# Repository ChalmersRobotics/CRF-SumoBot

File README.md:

# CRF nano-sumobot incl crf sumo hat

Please find :

- [instructions and workshop intro (v1.2, updated 251105) -here](https://github.com/ChalmersRobotics/CRF-SumoBot/releases/download/v1.2/CRF.miniSumo.kit.2025.workshop.intro.251105b.pdf)

- [3D manufacturing files](https://github.com/ChalmersRobotics/CRF-SumoBot/releases/download/v1.2/Sumobot.v7.3mf)

[complete release package - here!](https://github.com/ChalmersRobotics/CRF-SumoBot/releases)

# Changelog

| Version     | Changes      |
| ------------- | ------------- |
| v1.2          | <ul><li>Add EN_A and EN_B pins for controlling H-Bridge speed</li><li>Move start module placement slightly more towards the edge</li><li>Add header pins for unused ports on the Arduino to allow further extension / mods</li>Add an optional switch to pull-up and bypass start module</ul> |
| v1.1          | <ul><li>Move mounting holes slightly</li><li>Add header pins for start module</li></ul> |
| v1.0          | First draft |

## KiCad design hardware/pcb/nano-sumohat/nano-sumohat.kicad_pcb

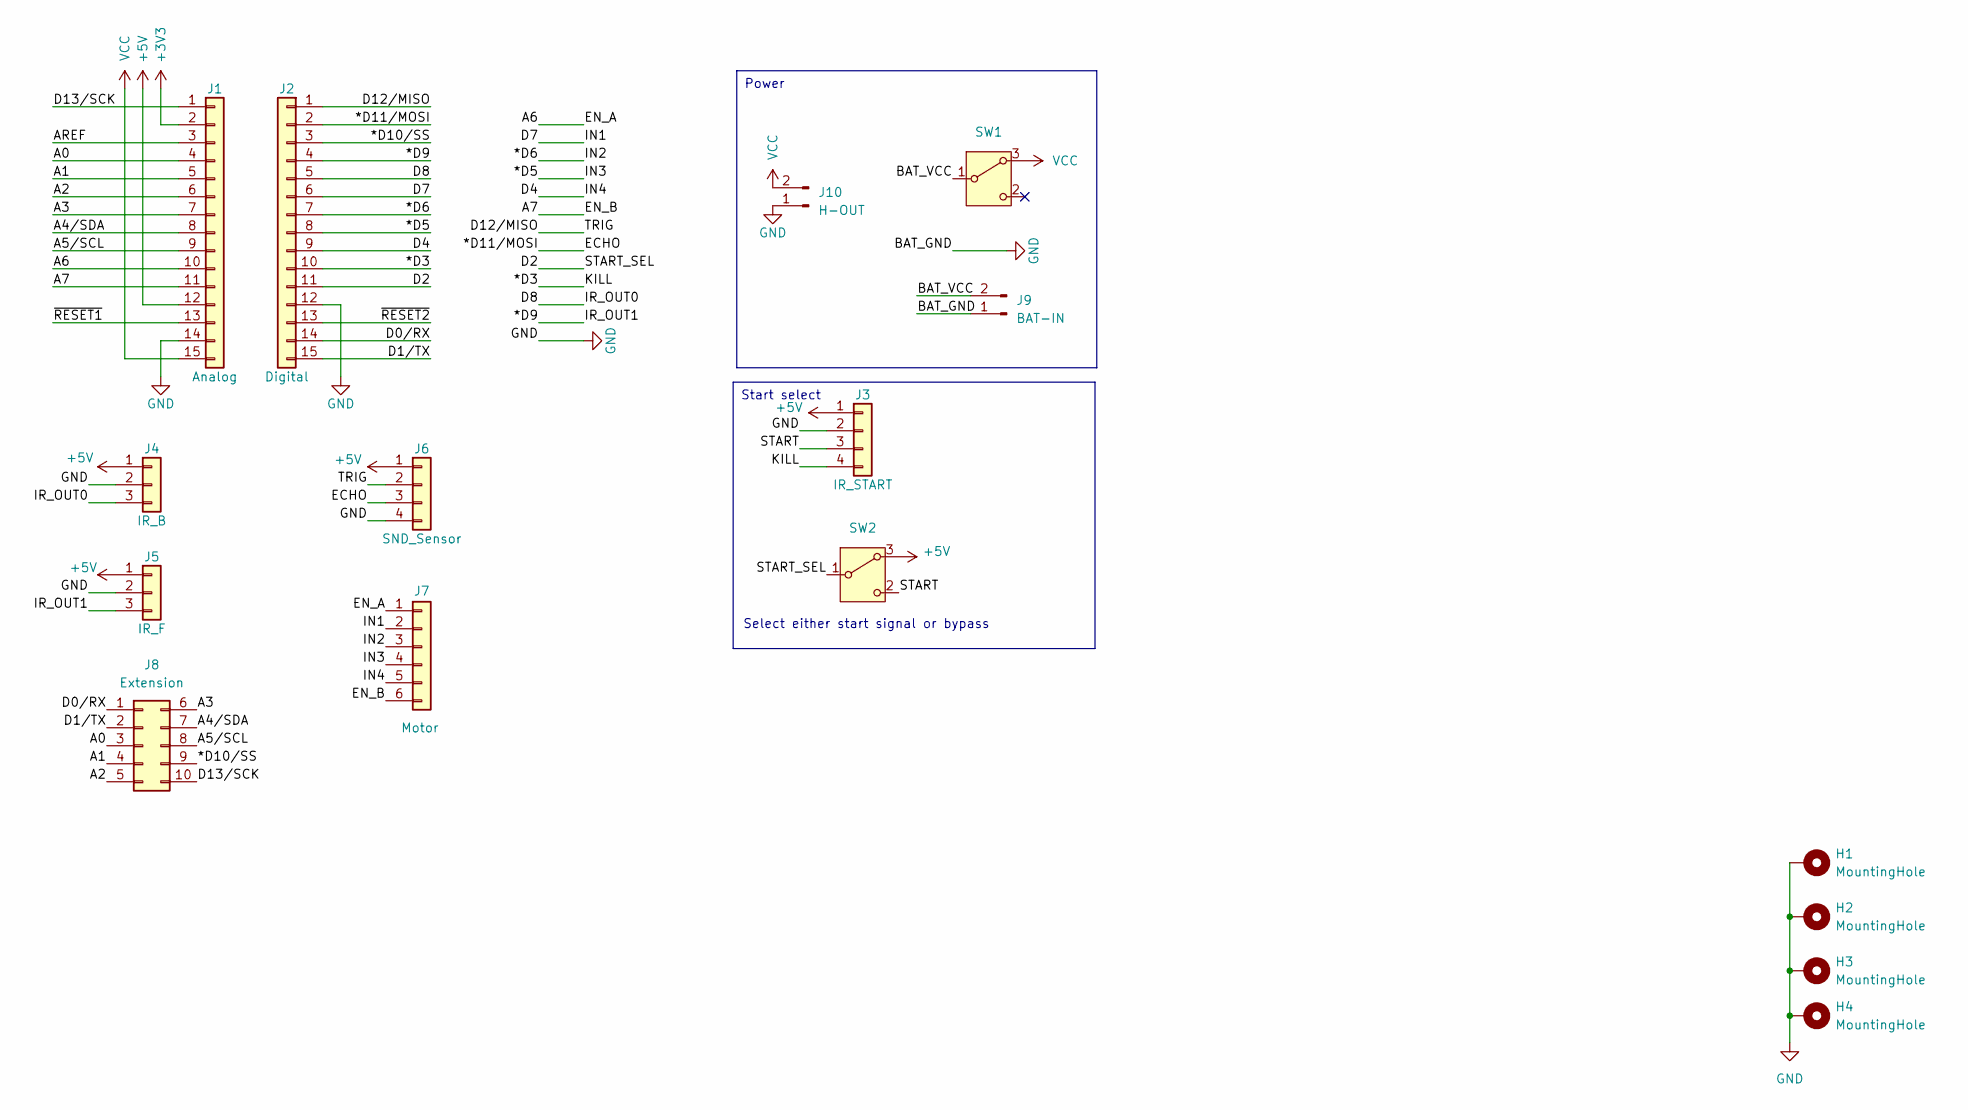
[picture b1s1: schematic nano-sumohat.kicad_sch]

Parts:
H1, H2, H3, H4: MountingHole; MountingHole_2.7mm_M2.5_DIN965_Pad_TopBottom
J1: Analog; PinSocket_1x15_P2.54mm_Vertical
J2: Digital; PinSocket_1x15_P2.54mm_Vertical
J3: IR_START; PinHeader_1x04_P2.54mm_Vertical
J4: IR_B; PinHeader_1x03_P2.54mm_Vertical
J5: IR_F; PinHeader_1x03_P2.54mm_Vertical
J6: SND_Sensor; PinSocket_1x04_P2.54mm_Vertical
J7: Motor; PinHeader_1x06_P2.54mm_Vertical
J8: Extension; PinHeader_2x05_P2.54mm_Vertical
J9: BAT-IN; JST_EH_B2B-EH-A_1x02_P2.50mm_Vertical
J10: H-OUT; JST_EH_B2B-EH-A_1x02_P2.50mm_Vertical
SW1, SW2: SW_Slide-03_Wuerth-WS-SLTV_10x2.5x6.4_P2.54mm

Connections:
+3V3: J1.2
+5V: J1.12, J3.1, J4.1, J5.1, J6.1, SW2.3 (A)
/*D3: J2.10, J3.4
/*D5: J2.8, J7.4
/*D6: J2.7, J7.3
/*D9: J2.4, J5.3
/*D10/SS: J2.3, J8.9
/*D11/MOSI: J2.2, J6.3
/A0: J1.4, J8.3
/A1: J1.5, J8.4
/A2: J1.6, J8.5
/A3: J1.7, J8.6
/A4/SDA: J1.8, J8.7
/A5/SCL: J1.9, J8.8
/A6: J1.10, J7.1
/A7: J1.11, J7.6
/AREF: J1.3
/BAT_VCC: J9.2, SW1.1 (B)
/D0/RX: J2.14, J8.1
/D1/TX: J2.15, J8.2
/D2: J2.11, SW2.1 (B)
/D4: J2.9, J7.5
/D7: J2.6, J7.2
/D8: J2.5, J4.3
/D12/MISO: J2.1, J6.2
/D13/SCK: J1.1, J8.10
/START: J3.3, SW2.2 (C)
/~RESET1: J1.13
/~RESET2: J2.13
GND: H1.1, H2.1, H3.1, H4.1, J1.14, J2.12, J3.2, J4.2, J5.2, J6.4, J9.1, J10.1
VCC: J1.15, J10.2, SW1.3 (A)

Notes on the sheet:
Power
Start select
Select either start signal or bypass

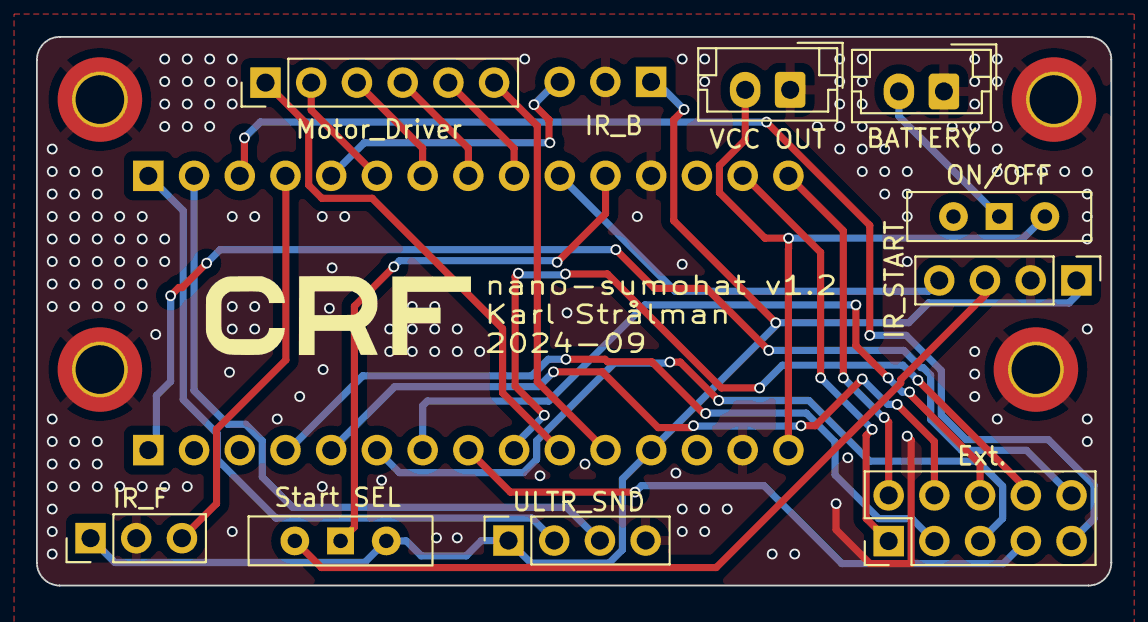
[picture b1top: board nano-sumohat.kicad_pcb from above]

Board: 2 copper layers, 59.7 x 30.5 mm, 16 parts (0 on the bottom side), 27 nets.

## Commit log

2022-11-16 Add sumobot project files
2023-03-18 Add PCB files and restructure repo
    Kicad project files and gerber
2024-03-22 Add gitignore for kicad files
2024-03-22 Add v1.1 for nano sumohat
2024-03-22 Add preview image of sumohat
2024-03-30 Adjust code for nano sumohat 1.1
2024-03-30 Format code
2024-04-02 Refactor code to be somewhat working
2024-04-10 Add comment for when to use old bootloader
2024-04-10 Add guide v2 pdf for sumo build
2024-04-17 Add v2-draft6 build guide
2025-02-01 Remove rendered image of v1.1
2025-02-01 Remove obsolete guide
2025-02-01 Update schematics with more comments
2025-02-01 Remove obsolete readme for schematics
2025-02-01 Add readme with change history
2025-02-05 Bump readme with where to find instructions
2025-02-05 Bump readme with slides
2025-02-05 Replace old 3D files
    Find 3D files in releases
2025-02-05 Improvements to code
    Increase distance for ultra snd detect
    Add IR handling even when bot is not attacking
